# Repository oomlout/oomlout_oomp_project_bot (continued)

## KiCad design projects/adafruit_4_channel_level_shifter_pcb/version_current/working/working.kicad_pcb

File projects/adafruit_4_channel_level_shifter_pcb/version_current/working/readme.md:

# 4-Channel-Level-Shifter-PCB by adafruit  
This is a harvested standardized copy of a project from github.  
The original project can be found at:  
https://github.com/adafruit/4-Channel-Level-Shifter-PCB  
Please consult that link for additional, details, files, and license information.  
Note: It was auto harvested and if the original repo had more than one board file or anything out of the ordinary the files here are likely not representative.

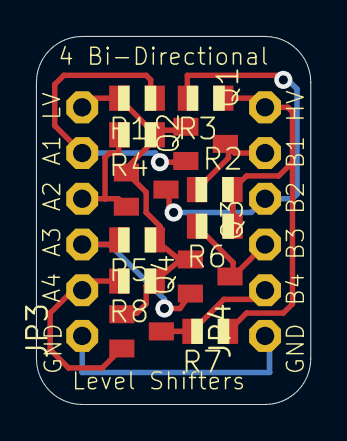
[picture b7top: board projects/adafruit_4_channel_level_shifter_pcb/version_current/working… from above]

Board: 16 copper layers, 15.2 x 20.4 mm, 15 parts (1 on the bottom side), 11 nets.

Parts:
JP3, JP4: 1X06-CLEANBIG
Q1, Q2, Q3, Q4: BSS138; SOT23
R1, R2, R3, R4, R5, R6, R7, R8: 10K; R0805
U$1: ADAFRUIT_3.5MM

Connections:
+3V3: JP3.6, Q1.1, Q2.1, Q3.1, Q4.1, R1.2, R4.1, R5.1, R8.1
+5V: JP4.6, R2.2, R3.1, R6.1, R7.1
GND: JP3.1, JP4.1
unnamed: JP4.3, Q3.3, R6.2
unnamed: JP4.5, Q1.3, R2.1
unnamed: JP3.3, Q3.2, R5.2
unnamed: JP3.2, Q4.2, R8.2
unnamed: JP4.2, Q4.3, R7.2
unnamed: JP3.4, Q2.2, R4.2
unnamed: JP4.4, Q2.3, R3.2
unnamed: JP3.5, Q1.2, R1.1

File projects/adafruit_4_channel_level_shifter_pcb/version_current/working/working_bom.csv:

"Id";"Designator";"Footprint";"Quantity";"Designation";"Supplier and ref";
1;"R2,R8,R3,R6,R5,R7,R4,R1";"R0805";8;"10K";;;
2;"JP3,JP4";"1X06-CLEANBIG";2;"";;;
3;"Q3,Q1,Q4,Q2";"SOT23";4;"BSS138";;;
4;"U$1";"ADAFRUIT_3.5MM";1;"";;;
